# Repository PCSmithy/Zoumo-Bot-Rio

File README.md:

# Zoumo-Bot-Rio
An Atmega32u4 and a set up motor drivers heavily modeled off the Sparkfun Arduino Pro Micro and the Adafruit Motor Driver Shield v2

https://www.sparkfun.com/products/12640

https://www.adafruit.com/product/1438

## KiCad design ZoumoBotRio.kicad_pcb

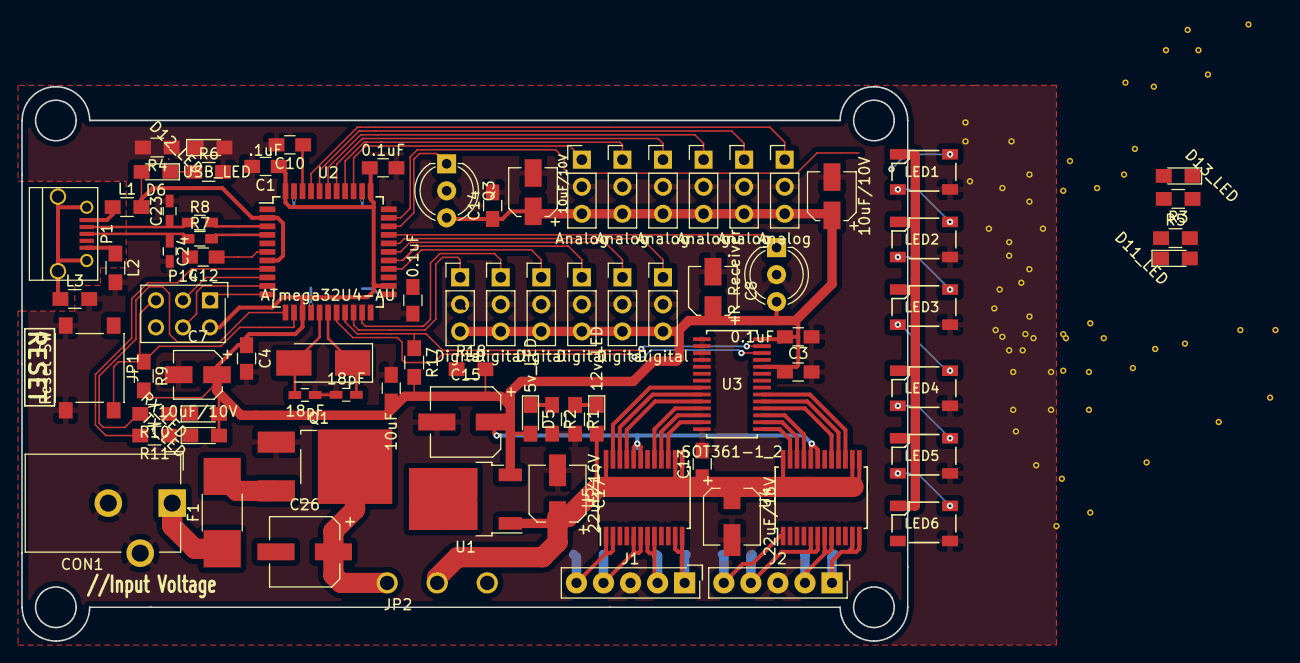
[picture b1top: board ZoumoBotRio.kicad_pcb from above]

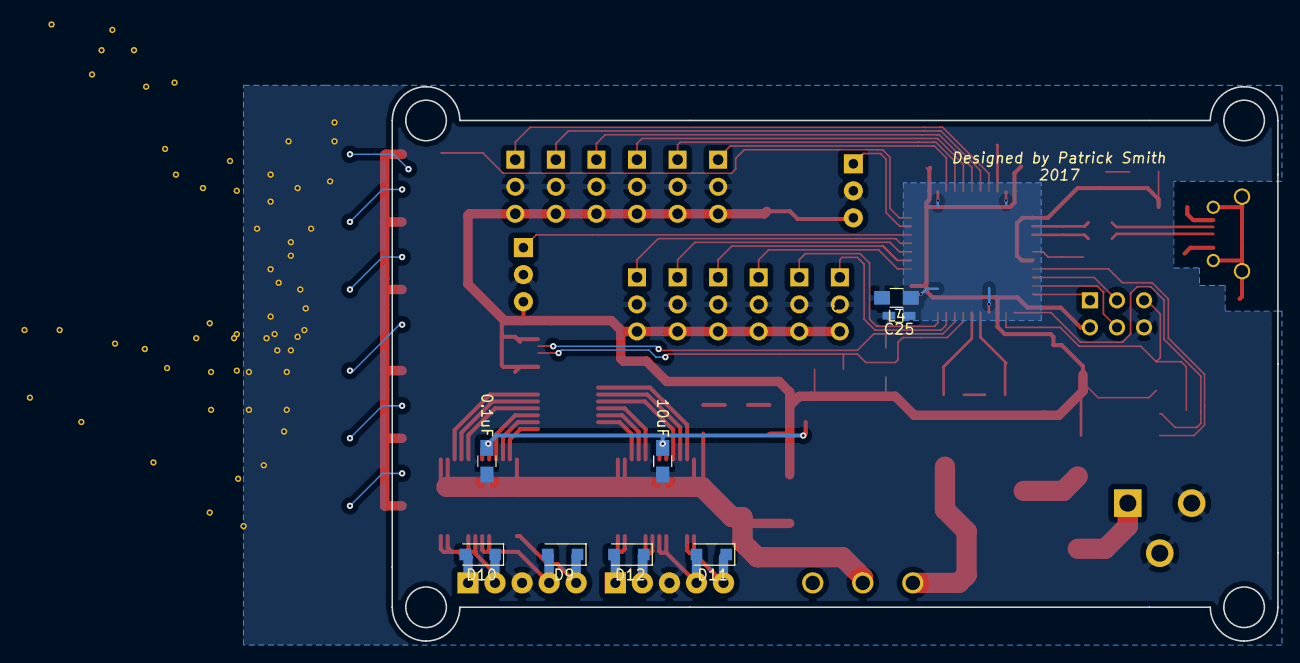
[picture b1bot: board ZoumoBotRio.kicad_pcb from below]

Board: 2 copper layers, 90 parts (8 on the bottom side), 73 nets.

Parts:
C1: .1uF; C_0805_HandSoldering
C2, C3, C4, C10, C14, C19, C20, C21: 0.1uF; C_0805_HandSoldering
C5, C6, C7, C8: 10uF/10V; CP_Elec_4x4.5
C9, C11: 18pF; C_0603_HandSoldering
C12: 1uF; C_0805_HandSoldering
C13: 0.33uF; C_0805_HandSoldering
C15: 100uF; CP_Elec_6.3x7.7
C16, C17: 22uF/16V; CP_Elec_5x5.8
C18, C22: 10uF; C_0805_HandSoldering
C23, C24, C25: C_Small; C_0603_HandSoldering
C26: C; CP_Elec_6.3x7.7
CON1: BARREL_JACK; Barrel_Jack_CUI_PJ-102AH
D1: 12v_LED; LED_0805_HandSoldering
D2: D13_LED; LED_0805_HandSoldering
D3: D12_LED; LED_0805_HandSoldering
D4: D11_LED; LED_0805_HandSoldering
D5: 5v_LED; LED_0805_HandSoldering
D6: USB_LED; LED_0805_HandSoldering
D7: RX_LED; LED_0805_HandSoldering
D8: TX_LED; LED_0805_HandSoldering
D9, D10, D11, D12: FlyBack; D_SOD-123F
F1: Polyfuse; R_1812_HandSoldering
J1, J2: Screw_Terminal_1x05; SL-105-X-XX_1x05
JP1: Reset SW; SW_SPST_PTS645
JP2: PWR SW; Slide SW
L1, L2, L3, L4: Ferrite_Bead_Small; R_0805_HandSoldering
LED1, LED2, LED3, LED4, LED5, LED6: NeoPixel; WS2812B_smallsilk
P1: USB_OTG; USB_Micro-B
P2, P4, P6, P8, P10, P12: Analog; Socket_Strip_Straight_1x03_Pitch2.54mm
P3, P5, P7, P9, P11, P13: Digital; Socket_Strip_Straight_1x03_Pitch2.54mm
P14: CONN_01X06; SDL-106-X-XX_2x03
Q1: Q_PMOS_GDS; TO-252-2_Rectifier
Q2, Q3: IR Receiver; LED_D5.0mm-3
R1: 500; R_0805_HandSoldering
R2, R3, R4, R5, R6: 150; R_0805_HandSoldering
R7, R8: 22; R_0603_HandSoldering
R9: 10K; R_0805_HandSoldering
R10, R11: 330; R_0805_HandSoldering
R17, R18: 10k; R_0805_HandSoldering
U1: ZLDO1117K50TC; TO-252-2
U2: ATmega32U4-AU; TQFP-44_10x10mm_Pitch0.8mm
U3: SOT361-1_2; PCA9685PW
U4, U5: TB6612FNG; SSOP-24_5.3x8.2mm_Pitch0.65mm
Y1: 16MHz; Crystal_SMD_Abracon_ABM3-2pin_5.0x3.2mm_HandSoldering

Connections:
+5V: C1.1, C2.1, C3.1, C4.1, C5.1, C6.1, C7.1, C8.1, C14.1, C15.1, C18.1, C19.1, C20.1, C21.1, C22.1, D5.2, D7.2, D8.2, LED1.3, LED2.3, LED3.3, LED4.3, LED5.3, LED6.3, P2.3, P3.3, P4.3, P5.3, P6.3, P7.3, P8.3, P9.3, P10.3, P11.3, P12.3, P13.3, P14.2, Q2.3, Q3.3, R9.2, R17.2, R18.2, U1.3, U2.14, U2.24, U2.34, U2.44, U3.24, U3.28, U4.19, U4.20, U5.19, U5.20
+12V: C13.1, C16.1, C17.1, D1.2, JP2.2, U1.1, U4.13, U4.14, U4.24, U5.13, U5.14, U5.24
/AREF: C10.1, U2.42
/MotorDriver/A01: D9.1, J2.5, U4.1, U4.2
/MotorDriver/A02: D9.2, J2.4, U4.5, U4.6
/MotorDriver/B01: D10.1, J2.2, U4.7, U4.8
/MotorDriver/B02: D10.2, J2.1, U4.11, U4.12
/MotorDriver/C01: D11.1, J1.5, U5.1, U5.2
/MotorDriver/C02: D11.2, J1.4, U5.5, U5.6
/MotorDriver/D01: D12.1, J1.2, U5.7, U5.8
/MotorDriver/D02: D12.2, J1.1, U5.11, U5.12
/MotorDriver/PWM2: U3.8, U5.23
/MotorDriver/PWM3: U3.9, U5.22
/MotorDriver/PWM4: U3.10, U5.21
/MotorDriver/PWM5: U3.11, U5.17
/MotorDriver/PWM6: U3.12, U5.16
/MotorDriver/PWM7: U3.13, U5.15
/MotorDriver/PWM8: U3.15, U4.23
/MotorDriver/PWM9: U3.16, U4.22
/MotorDriver/PWM10: U3.17, U4.21
/MotorDriver/PWM11: U3.18, U4.17
/MotorDriver/PWM12: U3.19, U4.16
/MotorDriver/PWM13: U3.20, U4.15
/Reset: JP1.1, P14.5, R9.1, U2.13
/SCL/D3: R18.1, U2.18, U3.26
/SDA/D2: R17.1, U2.19, U3.27
/dGnd: C25.1, L4.1, U2.15, U2.23, U2.35, U2.43
A0: P12.1, U2.41
A1: P10.1, U2.40
A2: P8.1, U2.39
A3: P6.1, U2.38
A4: P4.1, U2.37
A5: P2.1, U2.36
D0/RXI: P13.1, U2.20
D1/TXO: P11.1, U2.21
D4: P9.1, U2.26
D5: P7.1, U2.27
D6: P5.1, U2.28
D7: P3.1, U2.29
D8: Q2.1, U2.30
D9: Q3.1, U2.31
D10: LED1.2, U2.32
D+: C24.1, P1.3, R7.1, R7.2, U2.4
D-: C23.1, P1.2, R8.1, R8.2, U2.3
GND: C1.2, C2.2, C3.2, C4.2, C5.2, C6.2, C7.2, C8.2, C9.2, C10.2, C11.2, C12.2, C13.2, C14.2, C15.2, C16.2, C17.2, C18.2, C19.2, C20.2, C21.2, C22.2, C23.2, C24.2, C25.2, CON1.2, CON1.3, J1.3, J2.3, JP1.2, L2.2, L3.2, L4.2, LED1.1, LED2.1, LED3.1, LED4.1, LED5.1, LED6.1, P2.2, P3.2, P4.2, P5.2, P6.2, P7.2, P8.2, P9.2, P10.2, P11.2, P12.2, P13.2, P14.6, Q1.1, Q2.2, Q3.2, R1.2, R2.2, R3.2, R4.2, R5.2, R6.2, U1.2, U2.5, U2.33, U3.1, U3.2, U3.3, U3.4, U3.5, U3.14, U3.23, U3.25, U4.3, U4.4, U4.9, U4.10, U4.18, U5.3, U5.4, U5.9, U5.10, U5.18
MISO: P14.1, U2.11
MOSI: P14.4, U2.10
unnamed: C9.1, U2.17, Y1.1
unnamed: C11.1, U2.16, Y1.2
unnamed: C12.1, U2.6
unnamed: C26.1, JP2.1, Q1.2
unnamed: CON1.1, F1.1
unnamed: D1.1, R1.1
unnamed: D2.1, R3.1
unnamed: D3.1, R4.1
unnamed: D4.1, R5.1
unnamed: D5.1, R2.1
unnamed: D6.1, R6.1
unnamed: D7.1, R10.1
unnamed: D8.1, R11.1
unnamed: F1.2, Q1.3
unnamed: L1.1, P1.1
unnamed: L2.1, P1.5
unnamed: L3.1, P1.6
unnamed: LED1.4, LED2.2
unnamed: LED2.4, LED3.2
unnamed: LED3.4, LED4.2
unnamed: LED4.4, LED5.2
unnamed: LED5.4, LED6.2
unnamed: R10.2, U2.12
unnamed: R11.2, U2.8
SCK: P14.3, U2.9
UVcc: D6.2, L1.2, U2.2, U2.7

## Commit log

2017-11-10 Add files via upload
    Initial Upload of project files
2017-11-10 Updated PCB
    Updated PCB
2017-11-10 Tweaked Back Silkscreen
2017-11-11 Finished v2 layout, no traces
2017-11-12 Started drawing traces
2017-11-12 Continued laying out traces and copper pour
2017-11-12 Finished running traces and copper pour.
    I don't know how to do a nested copper pour zones, so the dGnd plane isn't implemented correctly, and isn't connected to the pads atmega gnd pads.
2017-11-13 Revised layout for EMI
    various issues.

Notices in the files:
parts and their libraries:
Copyright 2016 Accelerated Designs. All rights reserved.
